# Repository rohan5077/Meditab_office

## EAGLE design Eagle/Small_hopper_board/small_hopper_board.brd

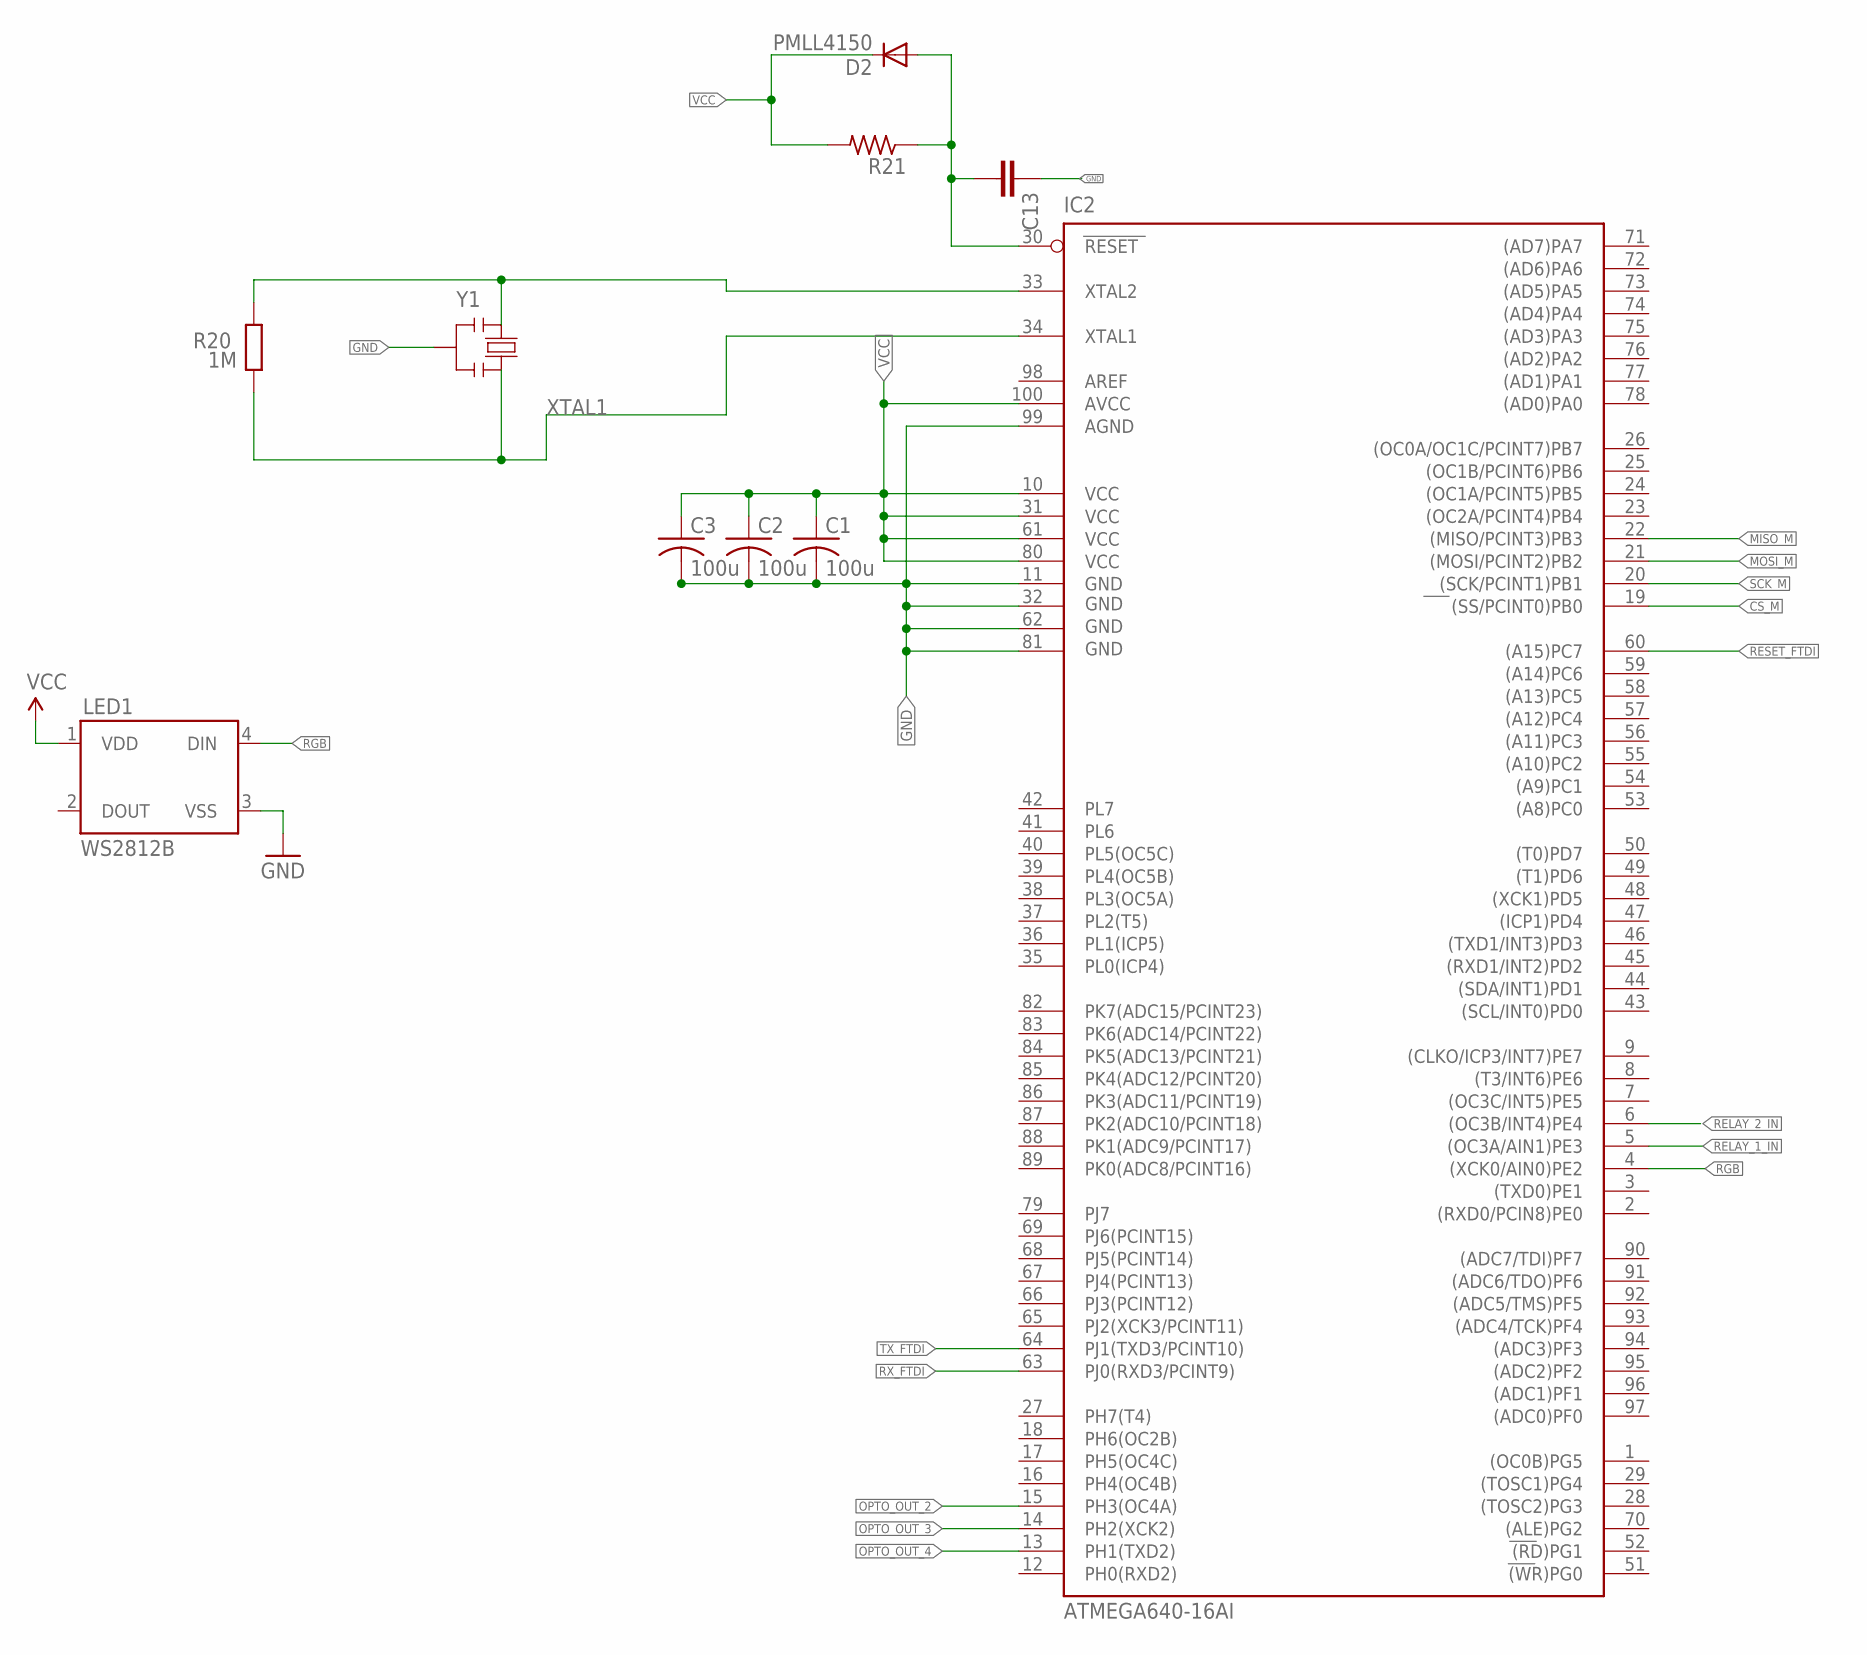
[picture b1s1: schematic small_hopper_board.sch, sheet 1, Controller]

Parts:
C1, C2, C3: 100u; C0603
C13: CC0603; C0603
D2: PMLL4150; SOD80C
IC2: ATMEGA640-16AI; TQFP100
LED1: WS2812B
R20: 1M; R0603-ROUND
R21: R-US_R0603; R0603
Y1: RESONATORMU; RESONATOR

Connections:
CS_M: IC2.19 ((SS/PCINT0)PB0); also elsewhere on the board
GND: C1.2, C2.2, C3.2, C13.1, IC2.11 (GND), IC2.32 (GND1), IC2.62 (GND2), IC2.81 (GND3), IC2.99 (AGND), LED1.3 (VSS), Y1.2; also elsewhere on the board
MISO_M: IC2.22 ((MISO/PCINT3)PB3); also elsewhere on the board
MOSI_M: IC2.21 ((MOSI/PCINT2)PB2); also elsewhere on the board
unnamed: C13.2, D2.A, IC2.30 (RESET), R21.1
OPTO_OUT_2: IC2.15 (PH3(OC4A)); also elsewhere on the board
OPTO_OUT_3: IC2.14 (PH2(XCK2)); also elsewhere on the board
OPTO_OUT_4: IC2.13 (PH1(TXD2)); also elsewhere on the board
RELAY_1_IN: IC2.5 ((OC3A/AIN1)PE3); also elsewhere on the board
RELAY_2_IN: IC2.6 ((OC3B/INT4)PE4); also elsewhere on the board
RESET_FTDI: IC2.60 ((A15)PC7); also elsewhere on the board
RGB: IC2.4 ((XCK0/AIN0)PE2), LED1.4 (DIN)
RX_FTDI: IC2.63 (PJ0(RXD3/PCINT9)); also elsewhere on the board
SCK_M: IC2.20 ((SCK/PCINT1)PB1); also elsewhere on the board
TX_FTDI: IC2.64 (PJ1(TXD3/PCINT10)); also elsewhere on the board
VCC: C1.1, C2.1, C3.1, D2.C, IC2.10 (VCC), IC2.31 (VCC1), IC2.61 (VCC2), IC2.80 (VCC3), IC2.100 (AVCC), LED1.1 (VDD), R21.2; also elsewhere on the board
XTAL1: IC2.34 (XTAL1), R20.1, Y1.3
XTAL2: IC2.33 (XTAL2), R20.2, Y1.1

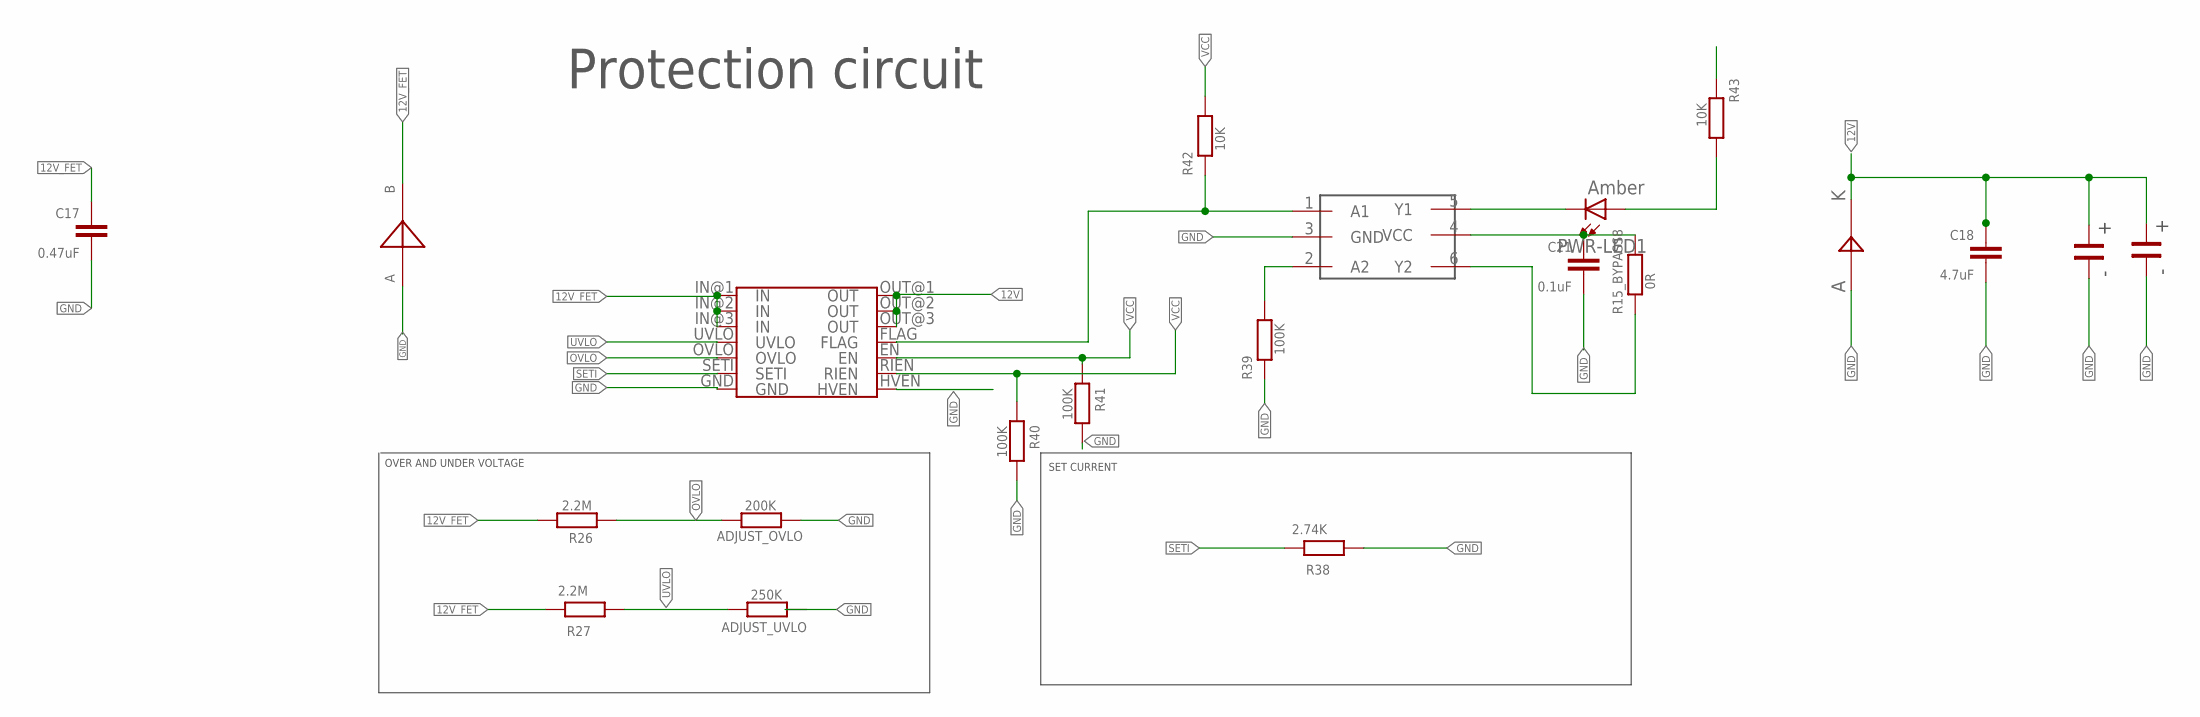
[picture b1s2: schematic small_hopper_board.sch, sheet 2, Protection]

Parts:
ADJUST_OVLO: 200K; R0603-ROUND
ADJUST_UVLO: 250K; R0603-ROUND
C17: 0.47uF; C0603-ROUND
C18: 4.7uF; C0603-ROUND
C21: 0.1uF; C0603-ROUND
PWR-LED1: Amber; LED-0603
R15_BYPASS8: 0R; R0603-ROUND
R26, R27: 2.2M; R0603-ROUND
R38: 2.74K; R0603-ROUND
R39, R40, R41: 100K; R0603-ROUND
R42, R43: 10K; R0603-ROUND
U$37: MAX14571; TSSOP14
U$38: STPS5L60S; SMC
U$39: SM6T36CA; DO214AA
U$40: NC7WZ07P6X; SC70-6L
U$41, U$42: EEV-FK1H331Q; EEVFK1H331Q

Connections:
12V: C18.1, U$37.OUT@1 (OUT), U$37.OUT@2 (OUT), U$37.OUT@3 (OUT), U$38.1, U$41.P$2, U$42.P$2; also elsewhere on the board
12V_FET: C17.1, R26.1, R27.1, U$37.IN@1 (IN), U$37.IN@2 (IN), U$37.IN@3 (IN), U$39.C; also elsewhere on the board
GND: ADJUST_OVLO.2, ADJUST_UVLO.2, C17.2, C18.2, C21.2, R38.2, R39.2, R40.1, R41.1, U$37.GND, U$37.HVEN, U$38.2, U$39.A, U$40.3 (GND), U$41.P$1, U$42.P$1; also elsewhere on the board
unnamed: PWR-LED1.A, R43.1
unnamed: PWR-LED1.C, U$40.5 (Y1)
unnamed: R39.1, U$40.2 (A2)
unnamed: R15_BYPASS8.2, U$40.6 (Y2)
OVLO: ADJUST_OVLO.1, R26.2, U$37.OVLO
SETI: R38.1, U$37.SETI
UVLO: ADJUST_UVLO.1, R27.2, U$37.UVLO
VCC: C21.1, R15_BYPASS8.1, R40.2, R41.2, R42.1, R43.2, U$37.EN, U$37.RIEN, U$40.4 (VCC); also elsewhere on the board
XX: R42.2, U$37.FLAG, U$40.1 (A1)

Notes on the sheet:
Protection circuit
OVER AND UNDER VOLTAGE
SET CURRENT

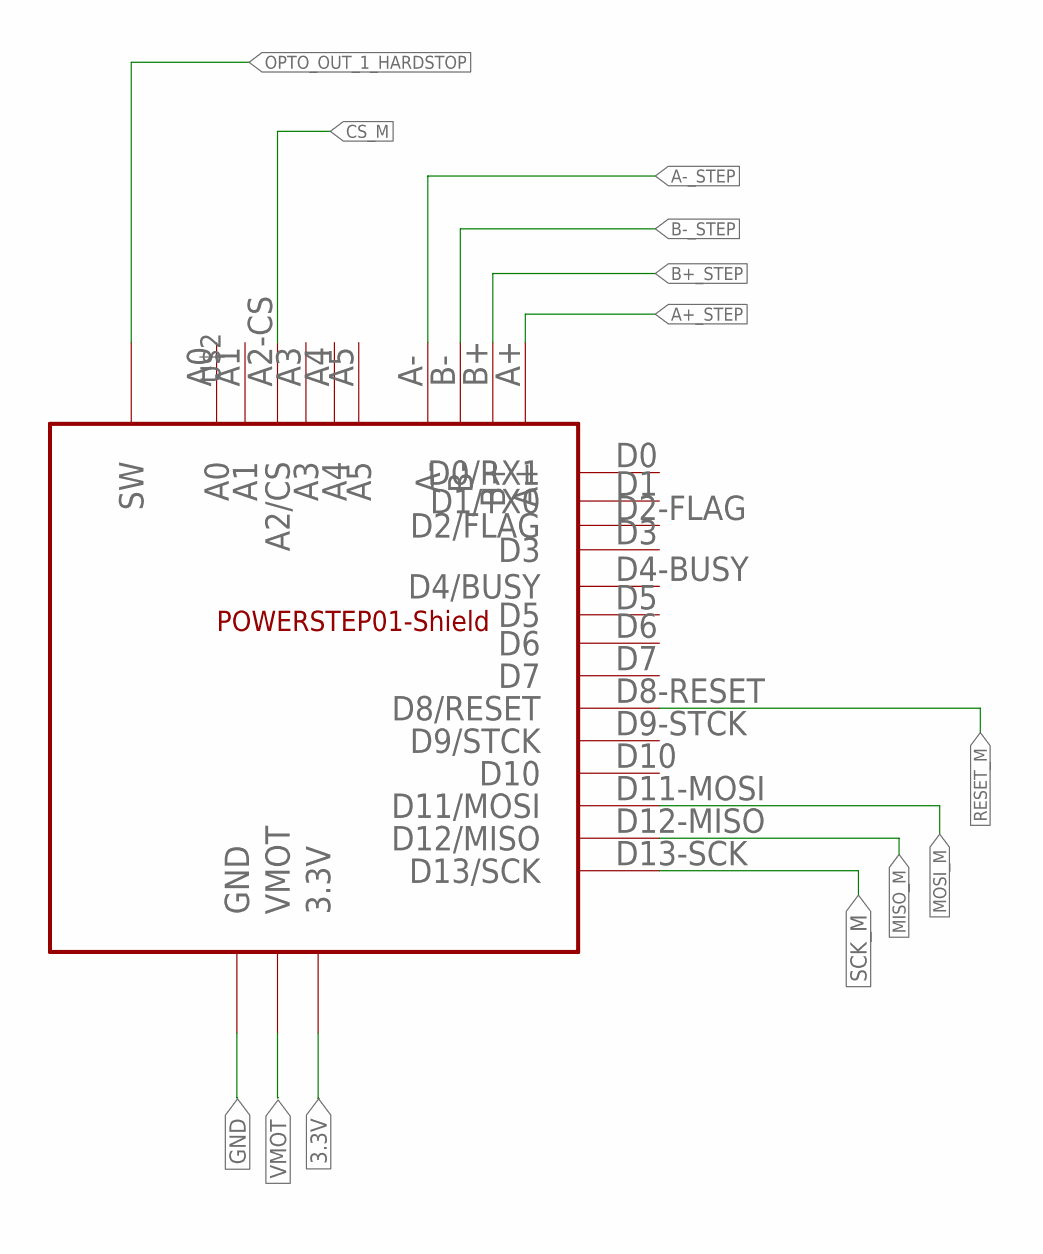
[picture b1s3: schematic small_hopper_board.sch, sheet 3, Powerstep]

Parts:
U$2: POWERSTEP01-SHIELD; POWERSTEP1

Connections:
3.3V: U$2.3.3V, U$2.IOREF (3.3V); also elsewhere on the board
A+_STEP: U$2.A+; also elsewhere on the board
A-_STEP: U$2.A-; also elsewhere on the board
B+_STEP: U$2.B+; also elsewhere on the board
B-_STEP: U$2.B-; also elsewhere on the board
CS_M: U$2.A2-CS (A2/CS); also elsewhere on the board
GND: U$2.GND@0 (GND), U$2.GND@1 (GND), U$2.GND@2 (GND), U$2.GND@3 (GND); also elsewhere on the board
MISO_M: U$2.D12-MISO (D12/MISO); also elsewhere on the board
MOSI_M: U$2.D11-MOSI (D11/MOSI); also elsewhere on the board
OPTO_OUT_1_HARDSTOP: U$2.SW; also elsewhere on the board
RESET_M: U$2.D8-RESET (D8/RESET)
SCK_M: U$2.D13-SCK (D13/SCK); also elsewhere on the board
VMOT: U$2.VS+ (VMOT); also elsewhere on the board

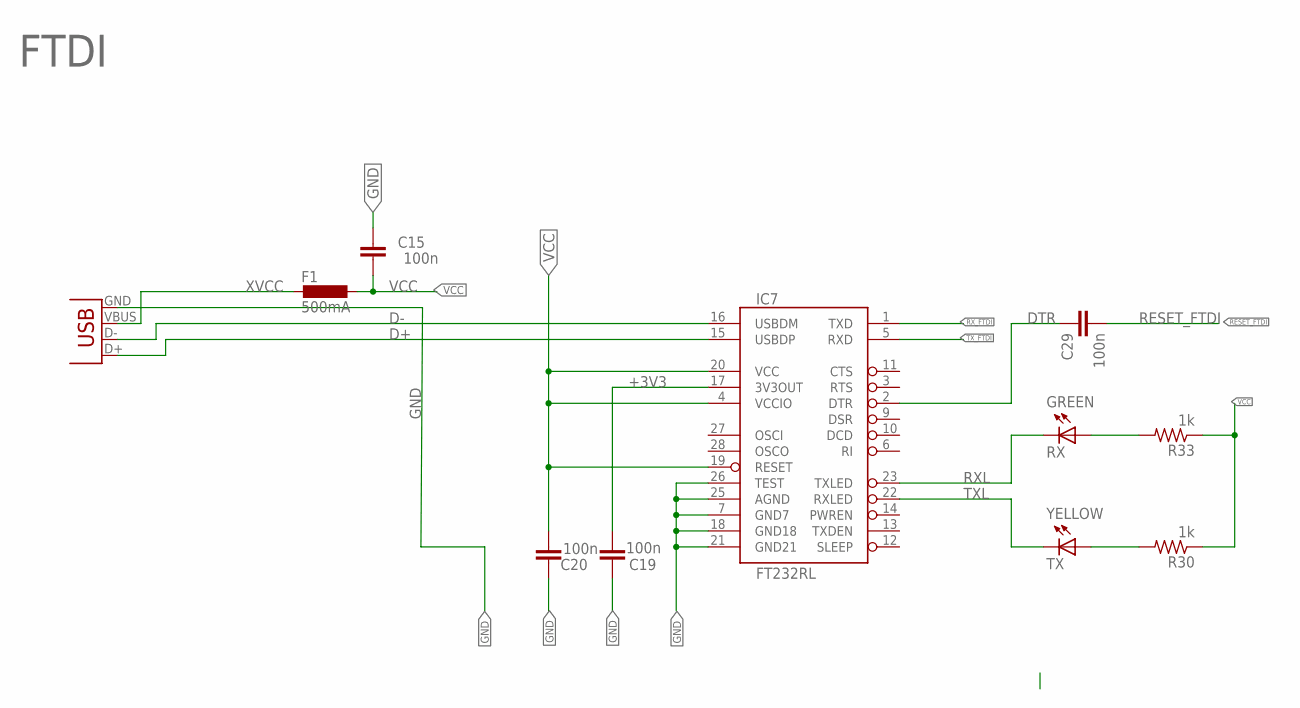
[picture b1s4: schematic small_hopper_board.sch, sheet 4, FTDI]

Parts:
C15: 100n; C0603
C19, C20, C29: 100n; C0603-ROUND
F1: 500mA; L1812
IC7: FT232RL; SSOP28DB
R30, R33: 1k; R0603
RX: GREEN; CHIPLED_0603
TX: YELLOW; CHIPLED_0603
USB: USB; USB-B-PTH-VERTICAL

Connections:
+3V3: C19.2, IC7.17 (3V3OUT)
D+: IC7.15 (USBDP), USB.D+
D-: IC7.16 (USBDM), USB.D-
DTR: C29.1, IC7.2 (DTR)
GND: C15.2, C19.1, C20.2, IC7.7 (GND7), IC7.18 (GND18), IC7.21 (GND21), IC7.25 (AGND), IC7.26 (TEST), USB.GND; also elsewhere on the board
unnamed: R30.2, TX.A
unnamed: R33.2, RX.A
RESET_FTDI: C29.2; also elsewhere on the board
RXL: IC7.23 (TXLED), RX.C
RX_FTDI: IC7.1 (TXD); also elsewhere on the board
TXL: IC7.22 (RXLED), TX.C
TX_FTDI: IC7.5 (RXD); also elsewhere on the board
VCC: C15.1, C20.1, F1.1, IC7.4 (VCCIO), IC7.19 (RESET), IC7.20 (VCC), R30.1, R33.1; also elsewhere on the board
XVCC: F1.2, USB.VBUS

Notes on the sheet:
FTDI

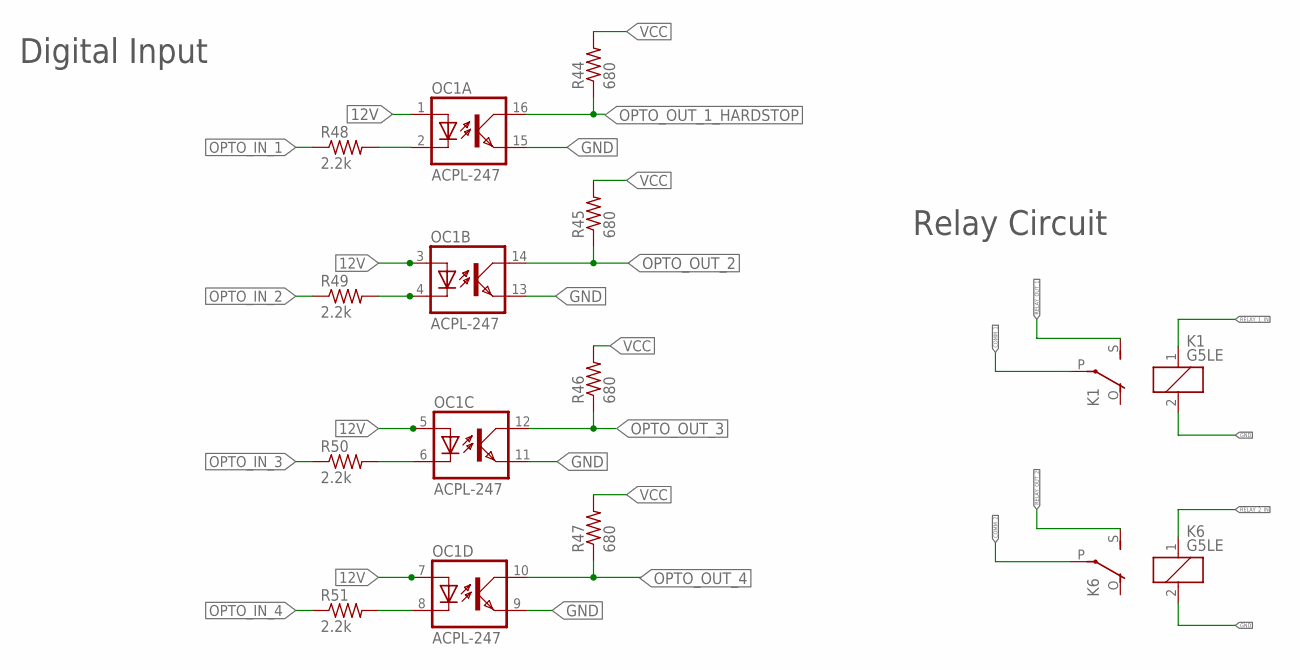
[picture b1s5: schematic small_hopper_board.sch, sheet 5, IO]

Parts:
K1, K6: G5LE
OC1: ACPL-247; SOP16
R44, R45, R46, R47: 680; R0603
R48, R49, R50, R51: 2.2k; R0603

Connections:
12V: OC1.1 (A), OC1.3 (A), OC1.5 (A), OC1.7 (A); also elsewhere on the board
COMM_1: K1.P; also elsewhere on the board
COMM_2: K6.P; also elsewhere on the board
GND: K1.2, K6.2, OC1.9 (EMIT), OC1.11 (EMIT), OC1.13 (EMIT), OC1.15 (EMIT); also elsewhere on the board
unnamed: OC1.4 (C), R49.2
unnamed: OC1.8 (C), R51.2
unnamed: OC1.6 (C), R50.2
unnamed: OC1.2 (C), R48.2
OPTO_IN_1: R48.1; also elsewhere on the board
OPTO_IN_2: R49.1; also elsewhere on the board
OPTO_IN_3: R50.1; also elsewhere on the board
OPTO_IN_4: R51.1; also elsewhere on the board
OPTO_OUT_1_HARDSTOP: OC1.16 (COL), R44.1; also elsewhere on the board
OPTO_OUT_2: OC1.14 (COL), R45.1; also elsewhere on the board
OPTO_OUT_3: OC1.12 (COL), R46.1; also elsewhere on the board
OPTO_OUT_4: OC1.10 (COL), R47.1; also elsewhere on the board
RELAY_1_IN: K1.1; also elsewhere on the board
RELAY_2_IN: K6.1; also elsewhere on the board
RELAY_OUT_1: K1.S; also elsewhere on the board
RELAY_OUT_2: K6.S; also elsewhere on the board
VCC: R44.2, R45.2, R46.2, R47.2; also elsewhere on the board

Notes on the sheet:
Digital Input
Relay Circuit

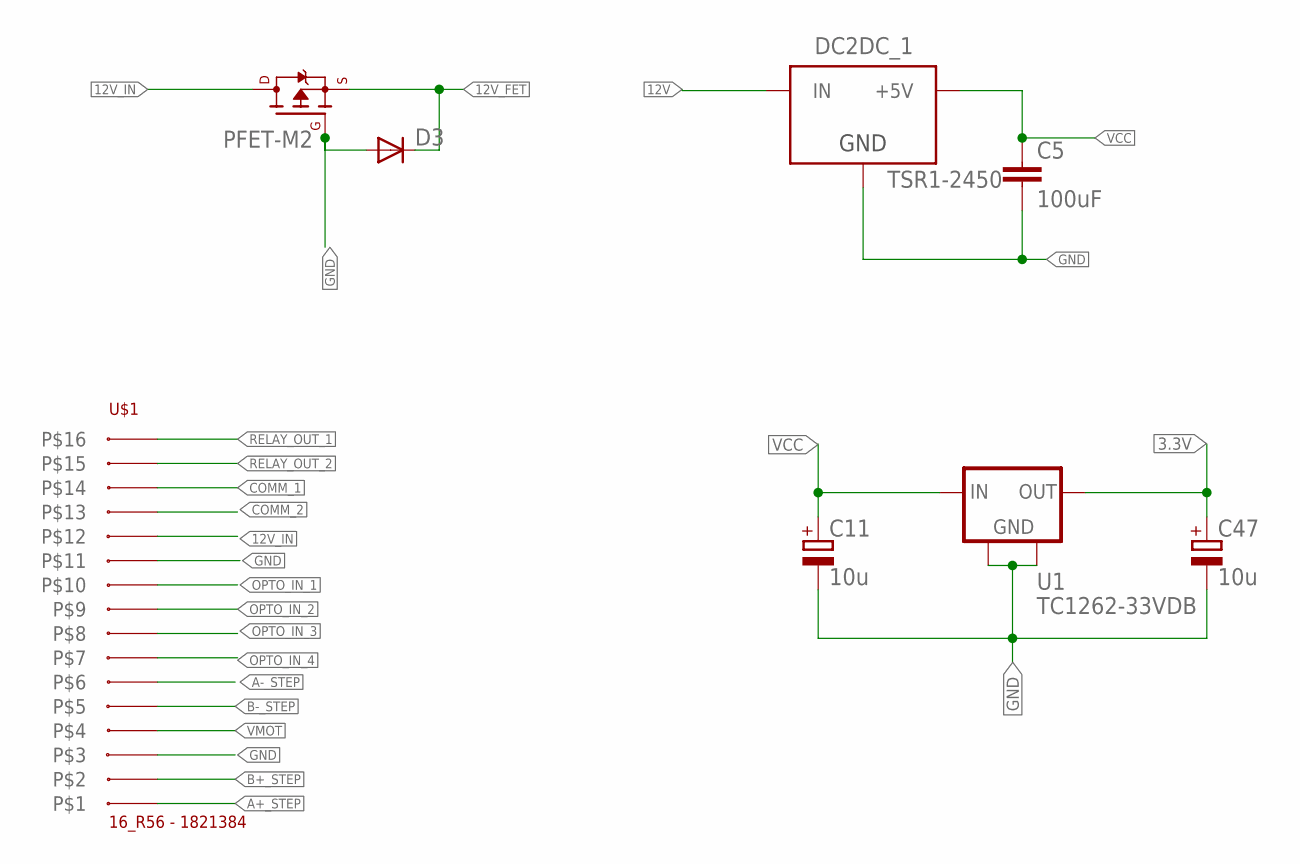
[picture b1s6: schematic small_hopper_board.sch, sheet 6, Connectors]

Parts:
C5: 100uF; C0603
C11, C47: 10u; 153CLV-0605
D3: DIODE-MINIMELF; MINIMELF
DC2DC_1: TSR1-2450; TSR-1
PFET-M2: FQP47P06NORMAL; FQP47P06-NORMAL
U1: TC1262-33VDB; SOT223
U$1: 16_R56 - 1821384

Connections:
3.3V: C47.+, U1.3 (OUT); also elsewhere on the board
12V: DC2DC_1.1 (IN); also elsewhere on the board
12V_FET: D3.C, PFET-M2.3 (S); also elsewhere on the board
12V_IN: PFET-M2.2 (D), U$1.P$12
A+_STEP: U$1.P$1; also elsewhere on the board
A-_STEP: U$1.P$6; also elsewhere on the board
B+_STEP: U$1.P$2; also elsewhere on the board
B-_STEP: U$1.P$5; also elsewhere on the board
COMM_1: U$1.P$14; also elsewhere on the board
COMM_2: U$1.P$13; also elsewhere on the board
GND: C5.2, C11.-, C47.-, D3.A, DC2DC_1.2 (GND), PFET-M2.1 (G), U1.2 (GND), U1.4 (GND), U$1.P$3, U$1.P$11; also elsewhere on the board
OPTO_IN_1: U$1.P$10; also elsewhere on the board
OPTO_IN_2: U$1.P$9; also elsewhere on the board
OPTO_IN_3: U$1.P$8; also elsewhere on the board
OPTO_IN_4: U$1.P$7; also elsewhere on the board
RELAY_OUT_1: U$1.P$16; also elsewhere on the board
RELAY_OUT_2: U$1.P$15; also elsewhere on the board
VCC: C5.1, C11.+, DC2DC_1.3 (+5V), U1.1 (IN); also elsewhere on the board
VMOT: U$1.P$4; also elsewhere on the board

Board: 2 copper layers, 62 parts (10 on the bottom side), 57 nets, no tracks yet.

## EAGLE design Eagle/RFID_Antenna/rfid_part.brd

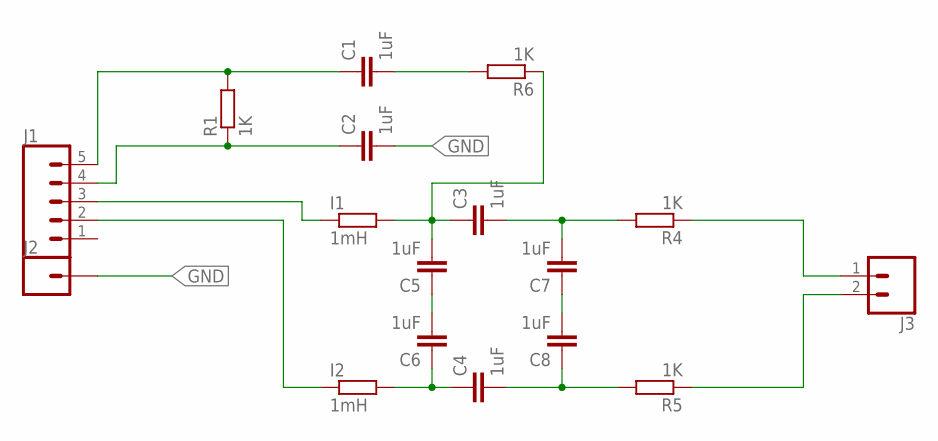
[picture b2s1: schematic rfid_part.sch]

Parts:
C1, C2, C3, C4, C5, C6, C7, C8: 1uF; C0603
I1, I2: 1mH; R0603
J1: CONN_05; 1X05
J2: CONN_01; 1X01
J3: CONN_02; 1X02
R1, R4, R5, R6: 1K; R0603

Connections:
GND: C2.2, J2.1
unnamed: C1.1, J1.5, R1.2
unnamed: C2.1, J1.4, R1.1
unnamed: I1.1, J1.3
unnamed: I2.1, J1.2
unnamed: C3.1, C5.2, I1.2, R6.1
unnamed: C5.1, C6.2
unnamed: C4.1, C6.1, I2.2
unnamed: C3.2, C7.2, R4.2
unnamed: C4.2, C8.1, R5.2
unnamed: C7.1, C8.2
unnamed: J3.1, R4.1
unnamed: J3.2, R5.1
unnamed: C1.2, R6.2

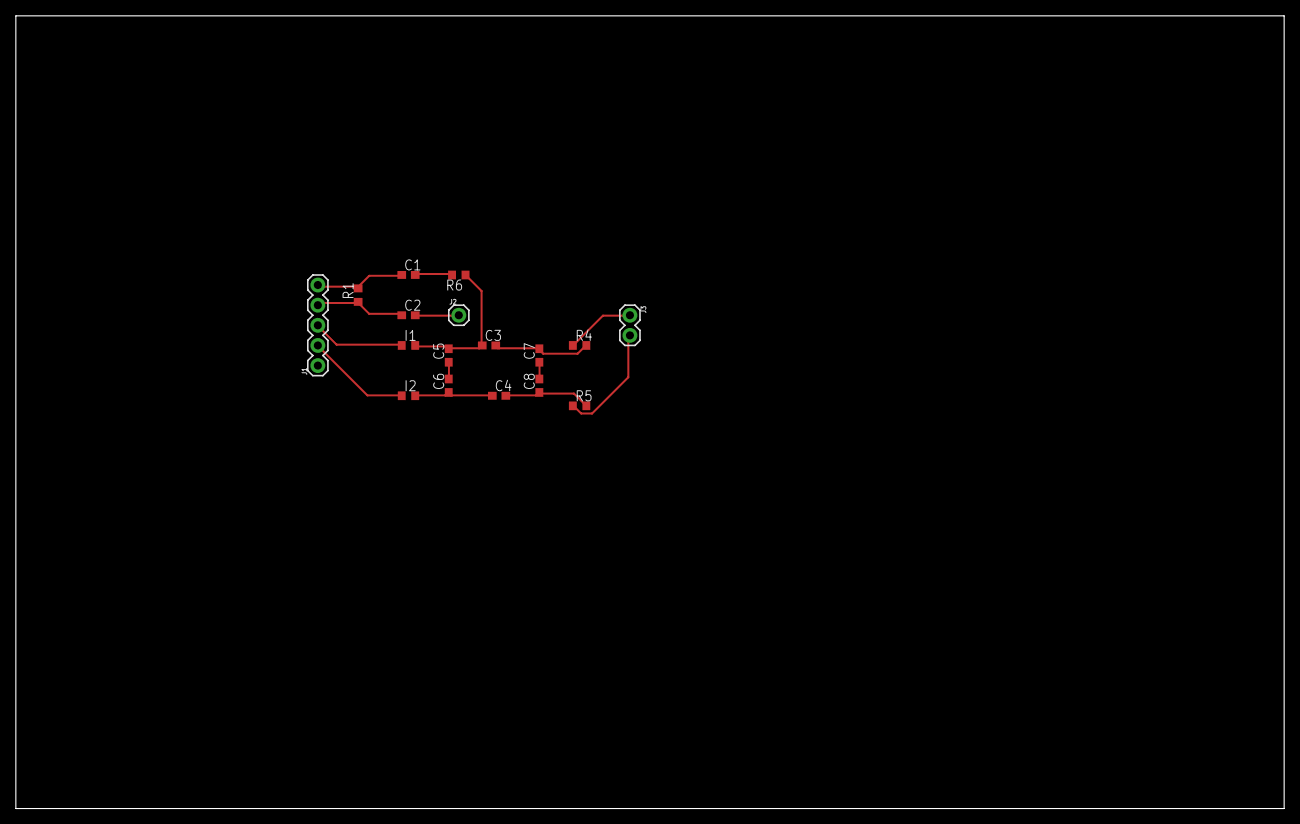
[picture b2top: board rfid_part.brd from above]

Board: 2 copper layers, 160.0 x 100.0 mm, 17 parts (0 on the bottom side), 14 nets.

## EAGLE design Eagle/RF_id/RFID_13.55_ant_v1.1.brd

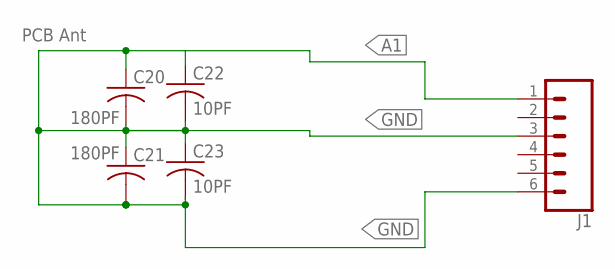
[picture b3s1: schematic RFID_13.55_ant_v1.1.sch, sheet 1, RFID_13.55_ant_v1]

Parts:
C20, C21: 180PF; C0603
C22, C23: 10PF; C0603
J1: CONN_06SILK_FEMALE_PTH; 1X06

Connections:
A1: C20.1, C22.1, J1.1
GND: C20.2, C21.1, C21.2, C22.2, C23.1, C23.2, J1.3, J1.6

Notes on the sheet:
PCB Ant

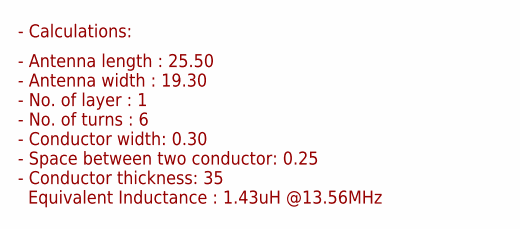
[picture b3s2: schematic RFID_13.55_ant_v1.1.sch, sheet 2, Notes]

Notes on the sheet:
- Calculations:
- Antenna length : 25.50 - Antenna width : 19.30 - No. of layer : 1 - No. of turns : 6 - Conductor width: 0.30 - Space between two conductor: 0.25 - Conductor thickness: 35 Equivalent Inductance : 1.43uH @13.56MHz

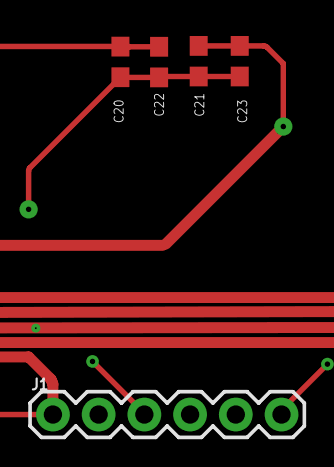
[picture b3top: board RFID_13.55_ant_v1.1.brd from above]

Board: 2 copper layers, 5 parts (0 on the bottom side), 2 nets.

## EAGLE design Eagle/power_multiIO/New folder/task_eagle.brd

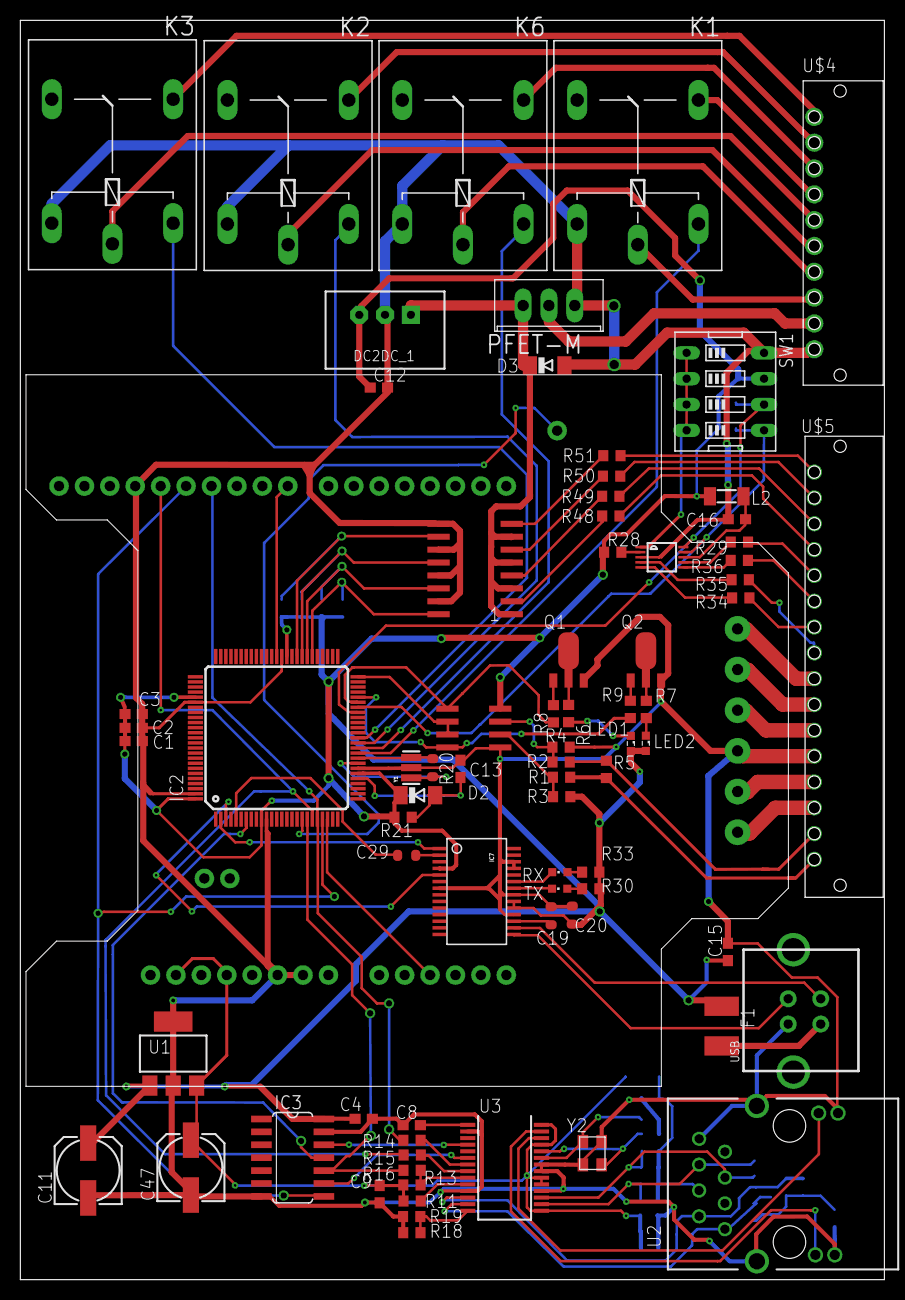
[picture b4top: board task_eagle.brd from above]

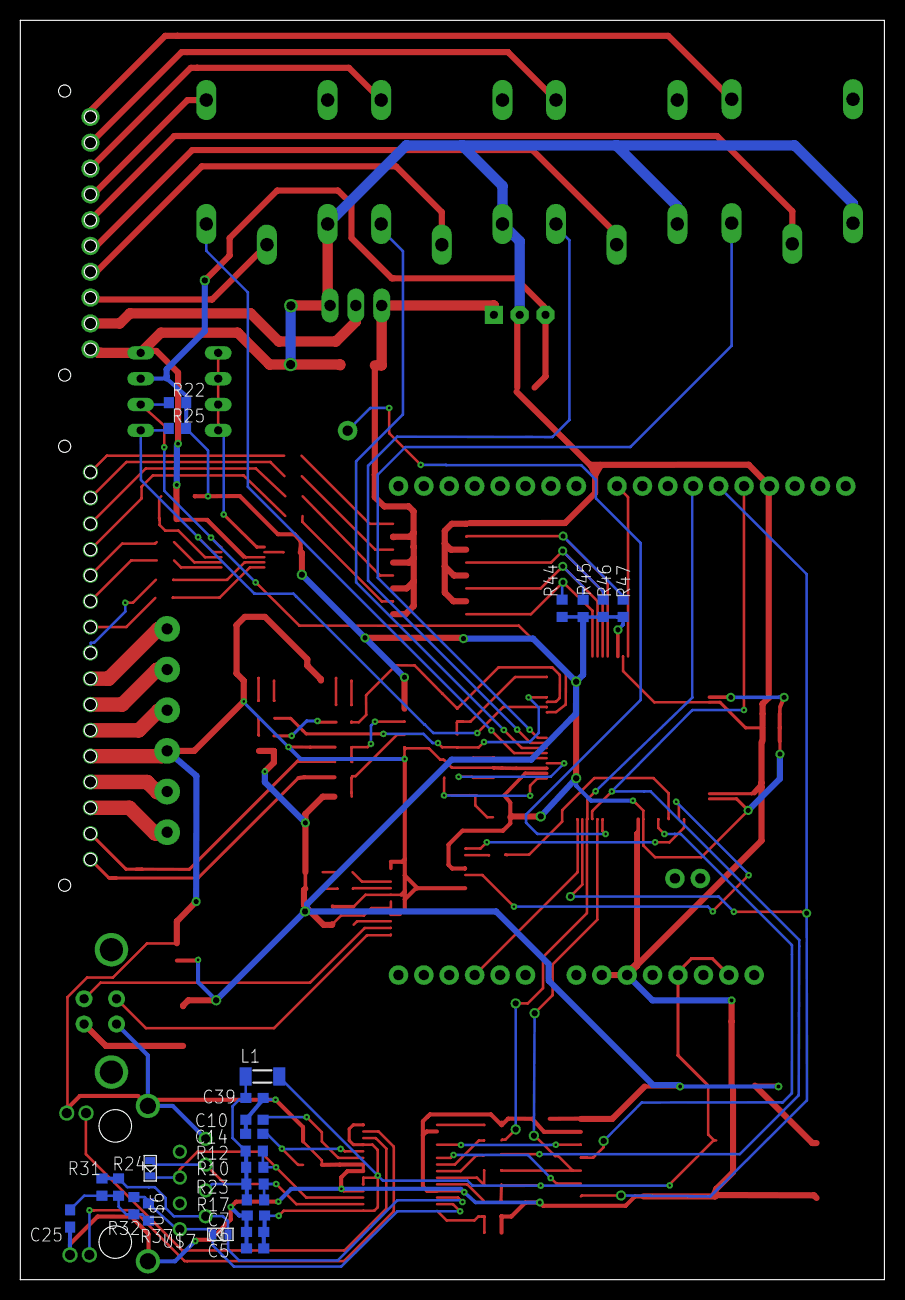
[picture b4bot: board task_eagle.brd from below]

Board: 2 copper layers, 85.0 x 123.9 mm, 100 parts (24 on the bottom side), 101 nets.

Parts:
C1, C2, C3: 100u; C0603
C4, C5, C6, C7, C8, C9, C15, C39: 100n; C0603
C10, C14: 22p; C0603
C11, C47: 10u; 153CLV-0605
C12: 100uF; C0603
C13: C0603
C16: 0.1nF; C0603
C19, C20, C29: 100n; C0603-ROUND
C25: 10n; C0603
D2: PMLL4150; SOD80C
D3: MINIMELF
DC2DC_1: TSR1-2450; TSR-1
F1: 500mA; L1812
IC2: ATMEGA640-16AI; TQFP100
IC3: 74ACT125D; SO14
IC7: FT232RL; SSOP28DB
IC8: MAX485; SO-08
K1, K2, K3, K6: G5LE
L1, L2: Ferrit Bead; SM-1206
LED1, LED2: LED_SML0603
OC1: ACPL-247; SOP16
PFET-M: FQP47P06-NORMAL
Q1, Q2: SOT89
R1, R2, R10, R12, R14, R15, R17, R23, R24, R31, R32, R37: 100; R0603
R3, R4: 5.6k; R0603
R5: 120ohm; R0603
R6, R7: 330; R0603
R8, R9, R22, R25, R28: 1K; R0603
R11, R13, R16, R21: R0603
R18: 15K; R0603
R19: 2K7; R0603
R20: 1M; R0603-ROUND
R29, R34, R35, R36: 3K3; R0603
R30, R33: 1k; R0603
R44, R45, R46, R47: 680; R0603
R48, R49, R50, R51: 2.2k; R0603
RX: GREEN; CHIPLED_0603
SW1: EDG-04
TX: YELLOW; CHIPLED_0603
U1: TC1262-33VDB; SOT223
U2: Tyco 5-6605758-1; 5-6605758-1
U3: ENC28J60-SSOP; SSOP28
U$1: ADS1115DGS; MSOP10
U$2: POWERSTEP01-SHIELD; POWERSTEP1
U$4: 10_R44 - 1821326
U$5: 16_R56 - 1821384
U$6, U$7: GG0402050R3C2P; 0402
USB: USB; USB-B-PTH-VERTICAL
Y1: RESONATOR
Y2: 25MHz; CRYSTAL-3.2-2.5

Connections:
3.3V: C5.1, C6.1, C7.1, C9.1, C47.+, L1.2, R11.2, R13.2, U1.3, U3.15, U3.19, U3.20, U3.25, U3.28, U$2.3.3V, U$2.IOREF
12V: D3.C, DC2DC_1.1, OC1.1, OC1.3, OC1.5, OC1.7, PFET-M.3
12V_IN: PFET-M.2, U$4.P$10
+3V3: C19.2, IC7.17
A: R1.2, R5.2, U$5.P$1
A0_ADC: R35.2, U$5.P$9
A1_ADC: R34.2, U$5.P$10
A2_ADC: R36.1, U$5.P$11
A3_ADC: R29.2, U$5.P$12
A+_STEP: U$2.A+, U$5.P$3
A-_STEP: U$2.A-, U$5.P$8
B: R2.2, R5.1, U$5.P$2
B+_STEP: U$2.B+, U$5.P$4
B-_STEP: U$2.B-, U$5.P$7
CCW: IC2.18, U$2.SW
COMM_1: K1.P, U$4.P$9
COMM_2: K6.P, U$4.P$8
COMM_3: K2.P, U$4.P$7
COMM_4: K3.P, U$4.P$6
CS: IC2.19, IC3.10, R16.2
CS_M: IC2.23, U$2.A2-CS
D1: IC2.56, OC1.16, R44.1
D2: IC2.57, OC1.14, R45.1
D3: IC2.58, OC1.12, R46.1
D4: IC2.59, OC1.10, R47.1
D+: IC7.15, USB.D+
D-: IC7.16, USB.D-
DIG1_48V: K1.S, U$4.P$5
DIG2_48V: K6.S, U$4.P$4
DIG3_48V: K2.S, U$4.P$3
DIG4_48V: K3.S, U$4.P$2
DIG_24V_IN_1: R48.1, U$5.P$13
DIG_24V_IN_2: R49.1, U$5.P$14
DIG_24V_IN_3: R50.1, U$5.P$15
DIG_24V_IN_4: R51.1, U$5.P$16
DTR: C29.1, IC7.2
GND: C1.2, C2.2, C3.2, C4.2, C5.2, C6.2, C7.2, C8.1, C9.2, C10.2, C11.-, C12.2, C13.1, C14.2, C15.2, C16.2, C19.1, C20.2, C25.2, C39.2, C47.-, D3.A, DC2DC_1.2, IC2.11, IC2.32, IC2.62, IC2.81, IC2.99, IC3.7, IC3.13, IC7.7, IC7.18, IC7.21, IC7.25, IC7.26, IC8.5, K1.2, K2.2, K3.2, K6.2, OC1.9, OC1.11, OC1.13, OC1.15, PFET-M.1, Q1.3, Q2.3, R4.1, R18.1, R19.1, SW1.8, U1.2, U1.4, U2.8, U2.D2, U2.D4, U2.M1, U2.M2, U3.2, U3.11, U3.18, U3.21, U3.22, U$1.3, U$2.GND@0, U$2.GND@1, U$2.GND@2, U$2.GND@3, U$4.P$11, U$5.P$5, USB.GND, Y1.2, Y2.2, Y2.4
INT: IC2.7, IC3.11
INT_3V3: IC3.12, U3.4
LED1: U2.D1, U3.27
LED2: U2.D3, U3.26
MISO_1: IC2.22, IC3.8, U$2.D12-MISO
MOSI_1: IC2.21, R14.2, U$2.D11-MOSI
unnamed: IC8.6, R1.1, R3.1
unnamed: IC8.7, R2.1, R4.2
unnamed: R30.2, TX.A
unnamed: SW1.1, SW1.2, SW1.3, SW1.4, U$1.1
unnamed: LED1.C, R6.2
unnamed: LED2.C, R7.2
unnamed: Q1.2, R6.1
unnamed: Q2.2, R7.1
unnamed: Q2.1, R9.1
unnamed: Q1.1, R8.1
unnamed: R11.1, U3.10
unnamed: R13.1, R16.1, U3.9
unnamed: R14.1, U3.7
unnamed: R18.2, R19.2, U3.14
unnamed: R15.1, U3.8
unnamed: C8.2, U3.1
unnamed: C13.2, D2.A, IC2.30, R21.1
unnamed: R34.1, U$1.5
unnamed: R35.1, U$1.4
unnamed: C10.1, U3.23, Y2.3
unnamed: C25.1, R24.1, R31.1, R32.1, R37.1
unnamed: C39.1, L1.1, R10.2, R12.2, R17.2, R23.2, U2.4
unnamed: R29.1, U$1.7
unnamed: C14.1, U3.24, Y2.1
unnamed: R28.2, U$1.2
unnamed: R36.2, U$1.6
unnamed: R33.2, RX.A
unnamed: OC1.4, R49.2
unnamed: OC1.8, R51.2
unnamed: OC1.6, R50.2
unnamed: OC1.2, R48.2
RE/DE_MAX: IC2.50, IC8.2, IC8.3
RELAY_1_IN: IC2.35, K1.1
RELAY_2_IN: IC2.36, K6.1
RELAY_3_IN: IC2.37, K2.1
RELAY_4_IN: IC2.38, K3.1
RESET_1: IC2.63, U$2.D8-RESET
RESET_FTDI: C29.2, IC2.5
RXL: IC7.23, RX.C
RX_FTDI: IC2.2, IC7.1
RX_MAX: IC2.45, IC8.1, R8.2
SCK_1: IC2.20, R15.2, U$2.D13-SCK
SCL_ADC: IC2.43, R22.1, SW1.6, U$1.10
SDA_ADC: IC2.44, R25.1, SW1.5, U$1.9
SO_3V3: IC3.9, U3.6
TPIN+: R32.2, R37.2, U2.1, U3.13, U$7.C
TPIN-: R24.2, R31.2, U2.2, U3.12, U$7.A
TPOUT+: R10.1, R12.1, U2.5, U3.17, U$6.C
TPOUT-: R17.1, R23.1, U2.6, U3.16, U$6.A
TXL: IC7.22, TX.C
TX_FTDI: IC2.3, IC7.5
TX_MAX: IC2.46, IC8.4, R9.2
VCC: C1.1, C2.1, C3.1, C4.1, C11.+, C12.1, C15.1, C20.1, D2.C, DC2DC_1.3, F1.1, IC2.10, IC2.31, IC2.61, IC2.80, IC2.100, IC3.14, IC7.4, IC7.19, IC7.20, IC8.8, L2.2, LED1.A, LED2.A, R3.2, R21.2, R22.2, R25.2, R28.1, R30.1, R33.1, R44.2, R45.2, R46.2, R47.2, SW1.7, U1.1
VDD_IC: C16.1, L2.1, U$1.8
VMOT: U$2.VS+, U$5.P$6
XTAL1: IC2.34, R20.1, Y1.3
XTAL2: IC2.33, R20.2, Y1.1
XVCC: F1.2, USB.VBUS

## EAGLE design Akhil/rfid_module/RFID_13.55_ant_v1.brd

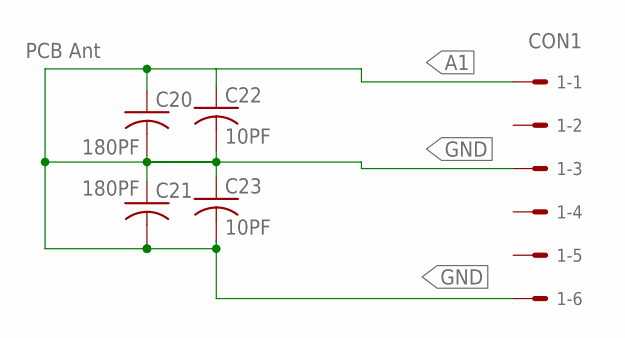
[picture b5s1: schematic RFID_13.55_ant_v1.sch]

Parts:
1: CON1; 6410-06
C20, C21: 180PF; C0603
C22, C23: 10PF; C0603

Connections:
A1: 1.1, C20.1, C22.1
GND: 1.3, 1.6, C20.2, C21.1, C21.2, C22.2, C23.1, C23.2

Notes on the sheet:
PCB Ant

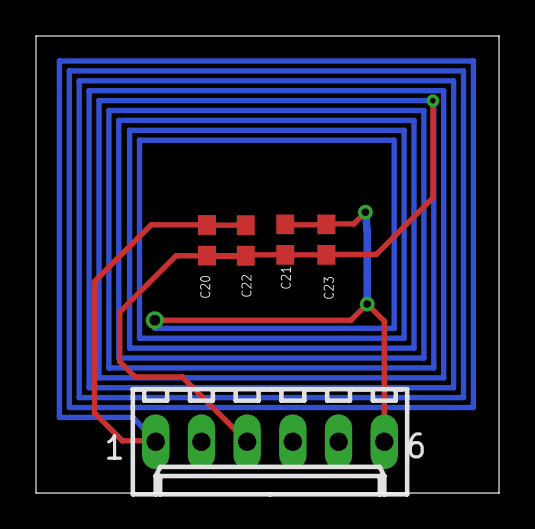
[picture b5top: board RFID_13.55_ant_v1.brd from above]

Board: 2 copper layers, 25.7 x 25.4 mm, 5 parts (0 on the bottom side), 2 nets.

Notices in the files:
parts and their libraries:
SparkFun-Connectors: Licensing: Creative Commons ShareAlike 4.0 International - https://creativecommons.org/licenses/by-sa/4.0
SparkFun-LED: Licensing: CC v3.0 Share-Alike You are welcome to use this library for commercial purposes.
